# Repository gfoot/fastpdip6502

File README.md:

# Fast PDIP 6502 project sources

This is my attempt at making a fast 6502-based computer, overclocking the CPU to 32MHz and 
beyond, while retaining a 70s/80s-style parallel architecture, with ISA-style expansion slots,
using only PDIP and through-hole components.

See https://hackaday.io/project/192630-fast-pdip-6502-computer for more details including
photos, schematics, and a more complete description of the development and theory of the
project.

This repository contains:

* hardware/breadboard - schematics and "PCB" layout files for the breadboard prototype
* hardware/pcb - schematics, PCB layouts, gerbers, etc for the all the PCBs
* pld - various PLD module code required by different versions
* server - Python serial server code
* src - 6502 assembler code
* utils - other utility scripts

See also other READMEs:
* [src/README.md](src/README.md)
* [hardware/pcb/README.md](hardware/pcb/README.md)
* [hardware/breadboard/README.md](hardware/breadboard/README.md)

# Building

The hardware files need to be loaded into KiCad 7.0 for editing, exporting gerbers, etc.

The gerber zips can be sent straight to a PCB manufacturer if you just want the same PCBs that
I am using.

The PLD files are built using WinCupl.  I do this from the command line but you can also do it
in the GUI if you prefer.

The 6502 assembler source is built using xa, which is easy to install under Ubuntu at least.  One build
step requires use of Python to create a #include file - I use Python 3 for this.  There's a Makefile in
the "src" directory.

The serial server program is also written in Python, for Python 3.

All of this is run on Ubuntu Linux but you should be able to port it to other systems.

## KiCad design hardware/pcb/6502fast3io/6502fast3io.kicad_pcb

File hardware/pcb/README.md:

# PCB design files

There are various KiCad projects that together make up the system.  The I/O module and CPU module are required
of course, the others are optional add-ons.

The gerbers for all the revisions I've made ("issues") are also included, along with exported schematics in PDF and PNG files
correspsonding to those revisions for easy reference.

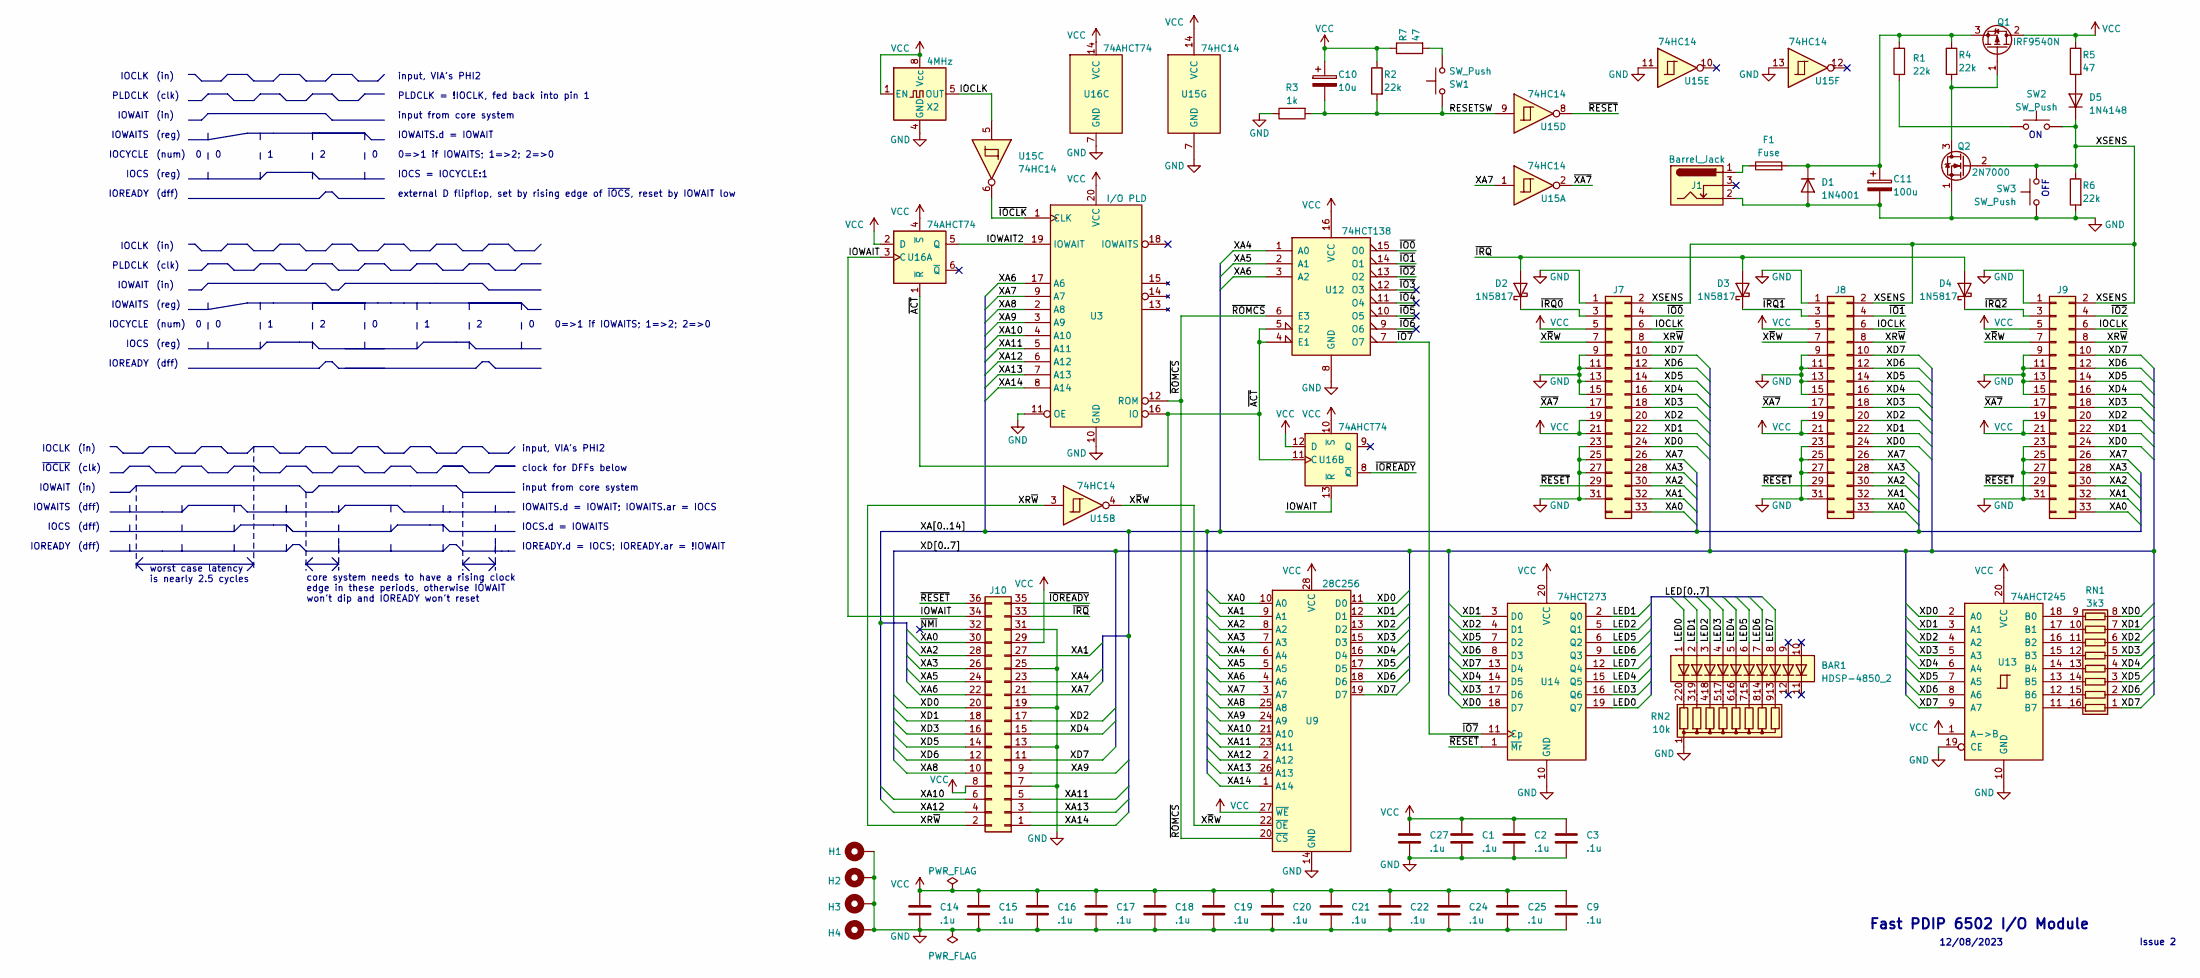
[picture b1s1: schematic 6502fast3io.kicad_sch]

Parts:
BAR1: HDSP-4850_2; HDSP-4850
C1, C2, C3, C9, C14, C15, C16, C17, C18, C19, C20, C21, C22, C24, C25, C27: .1u; C_Disc_D3.0mm_W1.6mm_P2.50mm
C10: 10u; CP_Radial_D5.0mm_P2.00mm
C11: 100u; CP_Radial_D5.0mm_P2.00mm
D1: 1N4001; D_DO-41_SOD81_P10.16mm_Horizontal
D2, D3, D4: 1N5817; D_DO-34_SOD68_P7.62mm_Horizontal
D5: 1N4148; D_DO-34_SOD68_P10.16mm_Horizontal
F1: Fuse; R_Axial_DIN0207_L6.3mm_D2.5mm_P10.16mm_Horizontal
H1, H2, H3, H4: MountingHole_Pad; MountingHole_2.2mm_M2_Pad
J1: Barrel_Jack; BarrelJack_Horizontal
J7, J8, J9: conn_pcb_edge_33pin_sense; 6502fast2_IO_PCBEdgeSocket
J10: Conn_02x18_Odd_Even; PCB_Edge_Socket_36pin
Q1: IRF9540N; TO-220-3_Horizontal_TabDown_NoHole
Q2: 2N7000; TO-92_Inline
R1, R2, R4, R6: 22k; R_Axial_DIN0204_L3.6mm_D1.6mm_P7.62mm_Horizontal
R3: 1k; R_Axial_DIN0204_L3.6mm_D1.6mm_P7.62mm_Horizontal
R5, R7: 47; R_Axial_DIN0204_L3.6mm_D1.6mm_P7.62mm_Horizontal
RN1: 3k3; DIP-16_W7.62mm
RN2: 10k; R_Array_SIP9
SW1, SW2, SW3: SW_Push; SW_PUSH_6mm_H4.3mm
U3: I/O PLD; DIP-20_W7.62mm_Socket
U9: 28C256; DIP-28_W15.24mm_Socket
U12: 74HCT138; DIP-16_W7.62mm
U13: 74AHCT245; DIP-20_W7.62mm
U14: 74HCT273; DIP-20_W7.62mm
U15: 74HC14; DIP-14_W7.62mm
U16: 74AHCT74; DIP-14_W7.62mm
X2: 4MHz; Oscillator_DIP-8

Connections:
/IOCLK: J7.6, J8.6, J9.6, U15.5, X2.5 (OUT)
/IOWAIT: J10.34, U16.3 (C), U16.13 (~R)
/IOWAIT2: U3.19 (IOWAIT), U16.5 (Q)
/LED0: BAR1.1 (A), U14.19 (Q7)
/LED1: BAR1.2 (A), U14.2 (Q0)
/LED2: BAR1.3 (A), U14.5 (Q1)
/LED3: BAR1.4 (A), U14.16 (Q6)
/LED4: BAR1.5 (A), U14.15 (Q5)
/LED5: BAR1.6 (A), U14.6 (Q2)
/LED6: BAR1.7 (A), U14.9 (Q3)
/LED7: BAR1.8 (A), U14.12 (Q4)
/RESETSW: C10.2, R2.2, R3.2, SW1.2, U15.9
/XA0: J7.33, J8.33, J9.33, J10.30, U9.10 (A0)
/XA1: J7.32, J8.32, J9.32, J10.27, U9.9 (A1)
/XA2: J7.30, J8.30, J9.30, J10.28, U9.8 (A2)
/XA3: J7.28, J8.28, J9.28, J10.26, U9.7 (A3)
/XA4: J10.23, U9.6 (A4), U12.1 (A0)
/XA5: J10.24, U9.5 (A5), U12.2 (A1)
/XA6: J10.22, U3.17 (A6), U9.4 (A6), U12.3 (A2)
/XA7: J7.26, J8.26, J9.26, J10.21, U3.9 (A7), U9.3 (A7), U15.1
/XA8: J10.10, U3.2 (A8), U9.25 (A8)
/XA9: J10.9, U3.3 (A9), U9.24 (A9)
/XA10: J10.6, U3.4 (A10), U9.21 (A10)
/XA11: J10.5, U3.5 (A11), U9.23 (A11)
/XA12: J10.4, U3.6 (A12), U9.2 (A12)
/XA13: J10.3, U3.7 (A13), U9.26 (A13)
/XA14: J10.1, U3.8 (A14), U9.1 (A14)
/XD0: J7.24, J8.24, J9.24, J10.20, RN1.8 (R8.1), U9.11 (D0), U13.2 (A0), U14.18 (D7)
/XD1: J7.22, J8.22, J9.22, J10.18, RN1.7 (R7.1), U9.12 (D1), U13.3 (A1), U14.3 (D0)
/XD2: J7.20, J8.20, J9.20, J10.17, RN1.6 (R6.1), U9.13 (D2), U13.4 (A2), U14.4 (D1)
/XD3: J7.18, J8.18, J9.18, J10.16, RN1.5 (R5.1), U9.15 (D3), U13.5 (A3), U14.17 (D6)
/XD4: J7.16, J8.16, J9.16, J10.15, RN1.4 (R4.1), U9.16 (D4), U13.6 (A4), U14.14 (D5)
/XD5: J7.14, J8.14, J9.14, J10.14, RN1.3 (R3.1), U9.17 (D5), U13.7 (A5), U14.7 (D2)
/XD6: J7.12, J8.12, J9.12, J10.12, RN1.2 (R2.1), U9.18 (D6), U13.8 (A6), U14.8 (D3)
/XD7: J7.10, J8.10, J9.10, J10.11, RN1.1 (R1.1), U9.19 (D7), U13.9 (A7), U14.13 (D4)
/XR~W: J7.8, J8.8, J9.8, J10.2, U15.3
/XSENS: D5.1 (K), J7.2, J8.2, J9.2, Q2.2 (G), R6.1, SW2.2, SW3.2
/X~RW: J7.7, J8.7, J9.7, U9.22 (~OE), U15.4
/~ACT: U3.16 (IO), U12.4 (E1), U12.5 (E2), U16.1 (~R), U16.11 (C)
/~IO0: J7.4, U12.15 (O0)
/~IO1: J8.4, U12.14 (O1)
/~IO2: J9.4, U12.13 (O2)
/~IO3: U12.12 (O3)
/~IO4: U12.11 (O4)
/~IO5: U12.10 (O5)
/~IO6: U12.9 (O6)
/~IO7: U12.7 (O7), U14.11 (Cp)
/~IOCLK: U3.1 (CLK), U15.6
/~IOREADY: J10.35, U16.8 (~Q)
/~IRQ0: D2.1 (K), J7.3
/~IRQ1: D3.1 (K), J8.3
/~IRQ2: D4.1 (K), J9.3
/~IRQ: D2.2 (A), D3.2 (A), D4.2 (A), J10.33
/~NMI: J10.32
/~RESET: J7.29, J8.29, J9.29, J10.36, U14.1 (~Mr), U15.8
/~ROMCS: U3.12 (ROM), U9.20 (~CS), U12.6 (E3)
/~XA7: J7.17, J8.17, J9.17, U15.2
GND: C1.2, C2.2, C3.2, C9.2, C11.2, C14.2, C15.2, C16.2, C17.2, C18.2, C19.2, C20.2, C21.2, C22.2, C24.2, C25.2, C27.2, D1.2 (A), H1.1, H2.1, H3.1, H4.1, J1.2, J7.1, J7.9, J7.11, J7.13, J7.15, J7.23, J7.25, J7.27, J7.31, J8.1, J8.9, J8.11, J8.13, J8.15, J8.23, J8.25, J8.27, J8.31, J9.1, J9.9, J9.11, J9.13, J9.15, J9.23, J9.25, J9.27, J9.31, J10.7, J10.13, J10.19, J10.25, J10.31, Q2.1 (S), R3.1, R6.2, RN2.1 (common), SW3.1, U3.10 (GND), U3.11 (OE), U9.14 (GND), U12.8 (GND), U13.10 (GND), U13.19 (CE), U14.10 (GND), U15.7 (GND), U15.11, U15.13, U16.7 (GND), X2.4 (GND)
unnamed: C11.1, D1.1 (K), F1.2, Q1.3 (S), R1.1, R4.1
unnamed: D5.2 (A), R5.2
unnamed: F1.1, J1.1
unnamed: Q1.1 (G), Q2.3 (D), R4.2
unnamed: R1.2, SW2.1
unnamed: R7.2, SW1.1
unnamed: RN1.16 (R1.2), U13.11 (B7)
unnamed: RN1.15 (R2.2), U13.12 (B6)
unnamed: RN1.14 (R3.2), U13.13 (B5)
unnamed: RN1.13 (R4.2), U13.14 (B4)
unnamed: RN1.12 (R5.2), U13.15 (B3)
unnamed: RN1.11 (R6.2), U13.16 (B2)
unnamed: RN1.10 (R7.2), U13.17 (B1)
unnamed: RN1.9 (R8.2), U13.18 (B0)
unnamed: BAR1.20 (K), RN2.2 (R1)
unnamed: BAR1.19 (K), RN2.3 (R2)
unnamed: BAR1.18 (K), RN2.4 (R3)
unnamed: BAR1.17 (K), RN2.5 (R4)
unnamed: BAR1.16 (K), RN2.6 (R5)
unnamed: BAR1.15 (K), RN2.7 (R6)
unnamed: BAR1.14 (K), RN2.8 (R7)
unnamed: BAR1.13 (K), RN2.9 (R8)
VCC: C1.1, C2.1, C3.1, C9.1, C10.1, C14.1, C15.1, C16.1, C17.1, C18.1, C19.1, C20.1, C21.1, C22.1, C24.1, C25.1, C27.1, J7.5, J7.19, J7.21, J8.5, J8.19, J8.21, J9.5, J9.19, J9.21, J10.8, J10.29, Q1.2 (D), R2.1, R5.1, R7.1, U3.20 (VCC), U9.27 (~WE), U9.28 (VCC), U12.16 (VCC), U13.1 (A->B), U13.20 (VCC), U14.20 (VCC), U15.14 (VCC), U16.2 (D), U16.4 (~S), U16.10 (~S), U16.12 (D), U16.14 (VCC), X2.1 (EN), X2.8 (Vcc)

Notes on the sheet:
(num)
IOCLK
OFF
12/08/2023
(dff)
IOCYCLE
IOCS.d = IOWAITS
input from core system
IOREADY
(in)
IOWAITS
IOWAIT
IOWAITS.d = IOWAIT
IOCS
(clk)
external D flipflop, set by rising edge of ~{IOCS}, reset by IOWAIT low
PLDCLK = !IOCLK, fed back into pin 1
worst case latency is nearly 2.5 cycles
core system needs to have a rising clock edge in these periods, otherwise IOWAIT won't dip and IOREADY won't reset
clock for DFFs below
(reg)
IOREADY.d = IOCS; IOREADY.ar = !IOWAIT
Issue 2
0=>1 if IOWAITS; 1=>2; 2=>0
PLDCLK
IOCS = IOCYCLE:1
Fast PDIP 6502 I/O Module
input, VIA's PHI2
~{IOCLK}
IOWAITS.d = IOWAIT; IOWAITS.ar = IOCS

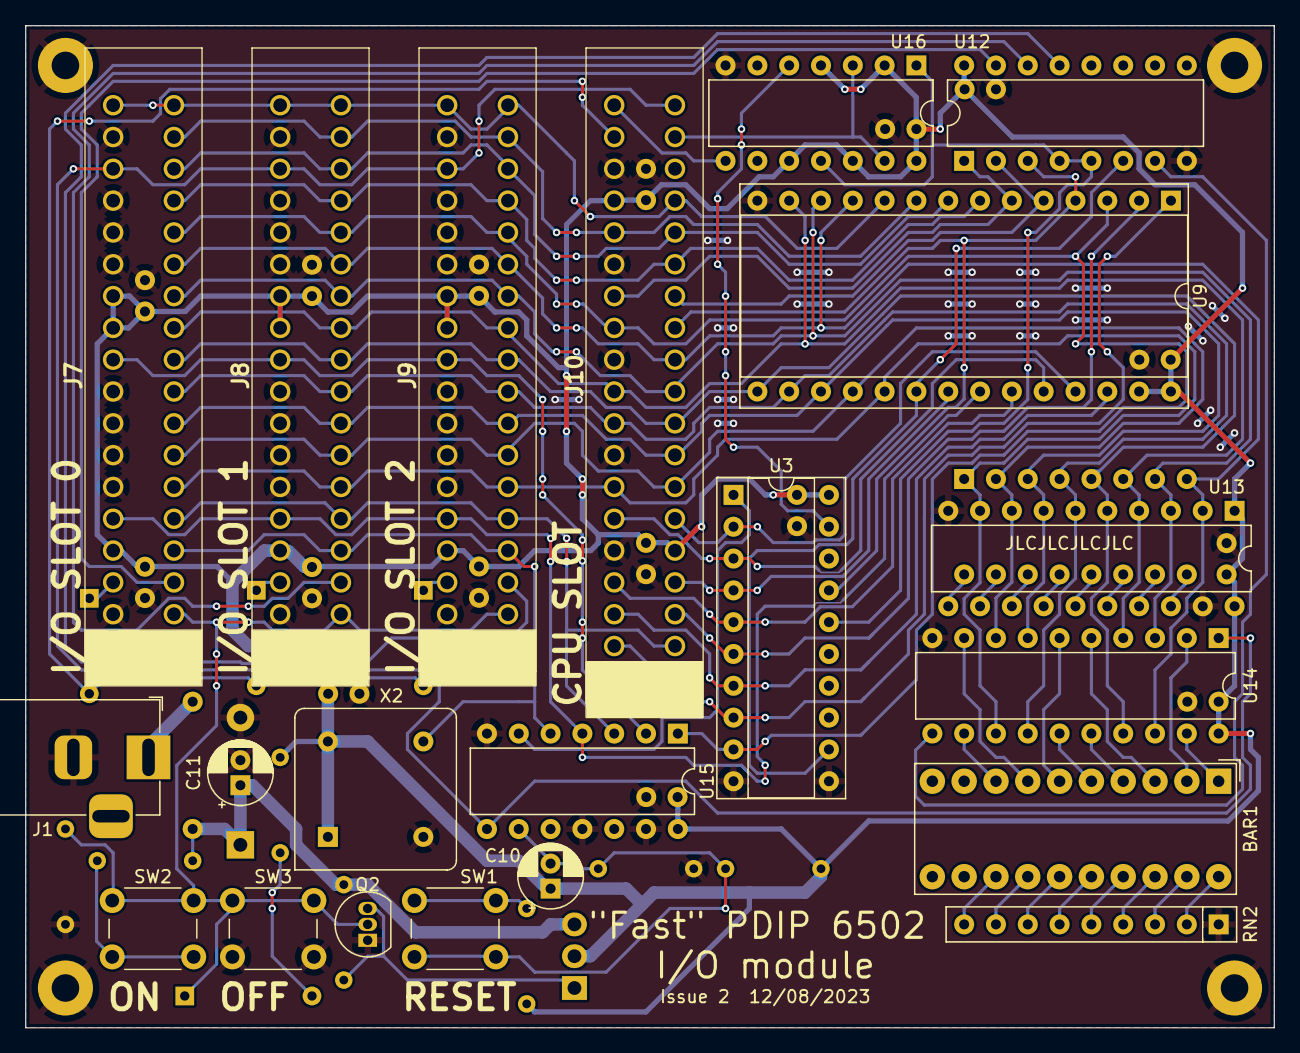
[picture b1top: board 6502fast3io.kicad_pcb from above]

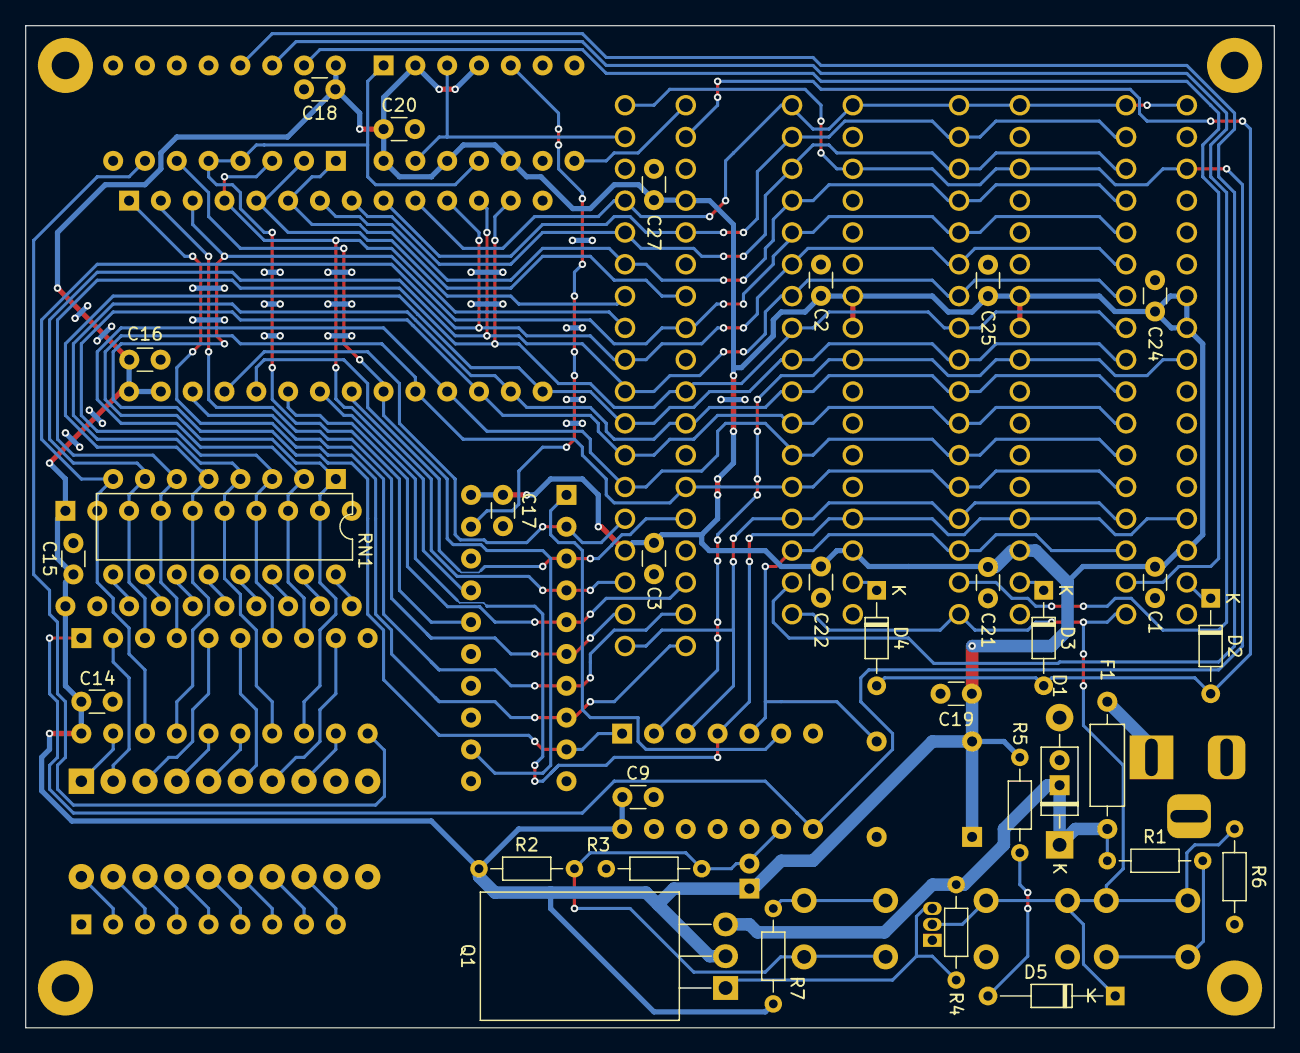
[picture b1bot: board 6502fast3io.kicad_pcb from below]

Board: 2 copper layers, 99.7 x 80.0 mm, 56 parts (31 on the bottom side), 76 nets.

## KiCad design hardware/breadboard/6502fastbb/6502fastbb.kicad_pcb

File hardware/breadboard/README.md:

# Breadboard circuit and layout

This project was used to define a slightly modified circuit for implementation on solderless
breadboards, and to plan the layout of the components.  It combines the CPU and I/O modules, but has
some parts removed which are only relevant to the PCB version such as I/O expansion sockets.

The PCB layout editor shows the positioning of the components on the breadboard, but not the connections between them.

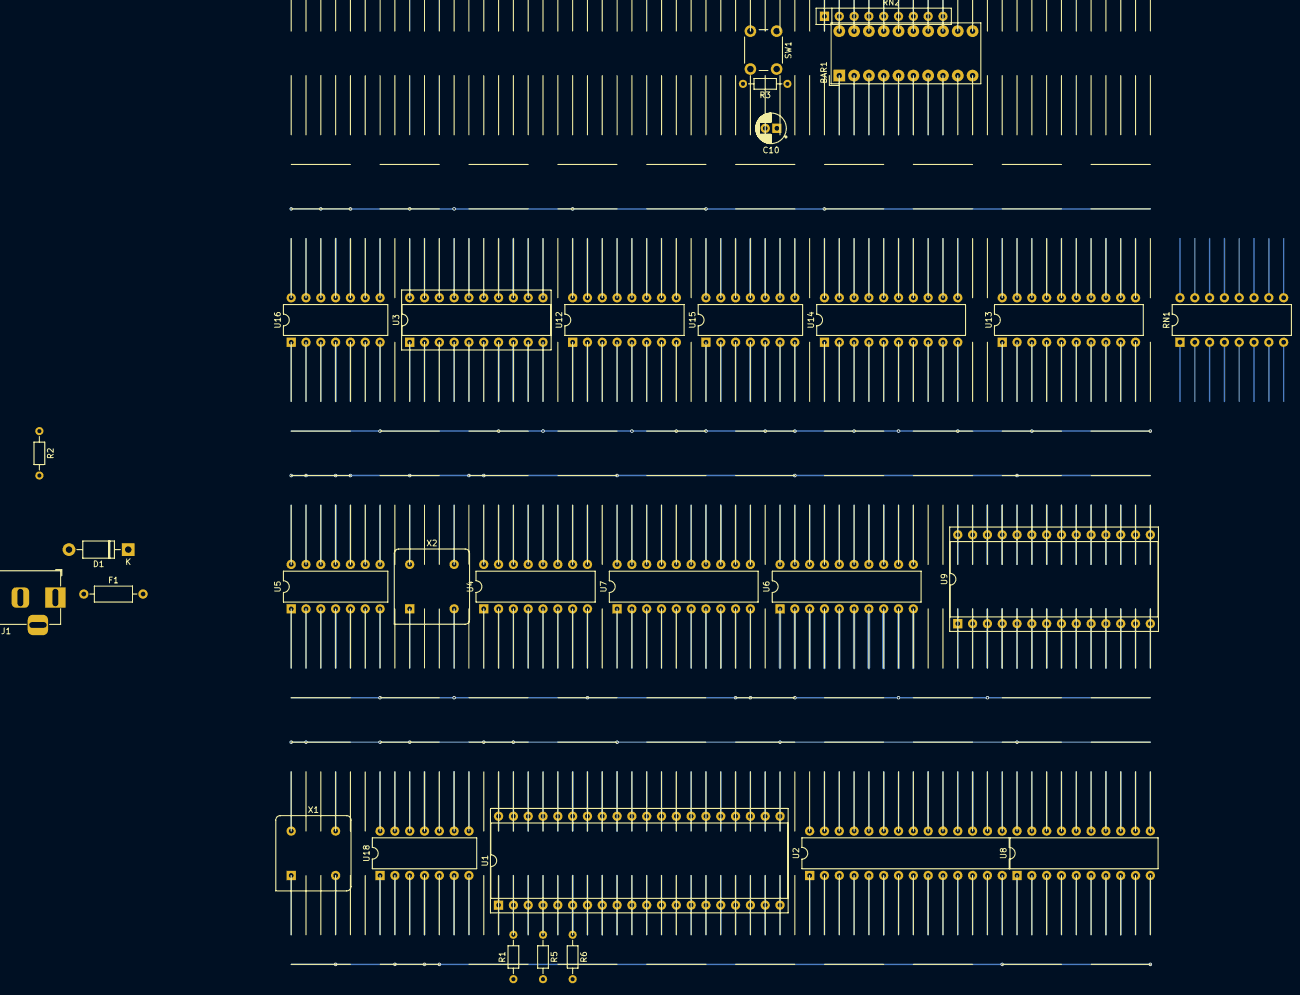
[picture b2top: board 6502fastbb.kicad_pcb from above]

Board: 2 copper layers, 30 parts (0 on the bottom side), 98 nets.

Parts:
BAR1: HDSP-4850_2; HDSP-4850
C10: 10u; CP_Radial_D5.0mm_P2.00mm
D1: 1N4001; D_DO-41_SOD81_P10.16mm_Horizontal
F1: Fuse; R_Axial_DIN0207_L6.3mm_D2.5mm_P10.16mm_Horizontal
J1: Barrel_Jack; BarrelJack_Horizontal
R1: 3k3; R_Axial_DIN0204_L3.6mm_D1.6mm_P7.62mm_Horizontal
R2: 1k; R_Axial_DIN0204_L3.6mm_D1.6mm_P7.62mm_Horizontal
R3: 22k; R_Axial_DIN0204_L3.6mm_D1.6mm_P7.62mm_Horizontal
R5, R6: 330; R_Axial_DIN0204_L3.6mm_D1.6mm_P7.62mm_Horizontal
RN1: 3k3; DIP-16_W7.62mm
RN2: 10k; R_Array_SIP9
SW1: SW_Push; SW_PUSH_6mm_H4.3mm
U1: WD65C02; DIP-40_W15.24mm_Socket
U2: 71256; DIP-28_W7.62mm
U3: I/O PLD; DIP-20_W7.62mm_Socket
U4: 74AHCT139; DIP-16_W7.62mm
U5: 74HC74; DIP-14_W7.62mm
U6, U7, U8: 74HC245; DIP-20_W7.62mm
U9: 28C256; DIP-28_W15.24mm_Socket
U12: 74HCT138; DIP-16_W7.62mm
U13: 74AHCT245; DIP-20_W7.62mm
U14: 74HCT273; DIP-20_W7.62mm
U15: 74HC14; DIP-14_W7.62mm
U16: 74AHCT74; DIP-14_W7.62mm
U18: 74LS32; DIP-14_W7.62mm
X1: CXO_DIP8; Oscillator_DIP-8
X2: 4MHz; Oscillator_DIP-8

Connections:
/A0: U1.9 (A0), U2.1 (A14), U7.2 (A0)
/A1: U1.10 (A1), U2.2 (A12), U7.3 (A1)
/A2: U1.11 (A2), U2.3 (A7), U7.4 (A2)
/A3: U1.12 (A3), U2.4 (A6), U7.5 (A3)
/A4: U1.13 (A4), U2.5 (A5), U7.6 (A4)
/A5: U1.14 (A5), U2.6 (A4), U7.7 (A5)
/A6: U1.15 (A6), U2.7 (A3), U7.8 (A6)
/A7: U1.16 (A7), U2.21 (A10), U6.2 (A0)
/A8: U1.17 (A8), U2.8 (A2), U6.3 (A1)
/A9: U1.18 (A9), U2.9 (A1), U6.4 (A2)
/A10: U1.19 (A10), U2.10 (A0), U6.5 (A3)
/A11: U1.20 (A11), U2.23 (A11), U6.6 (A4)
/A12: U1.22 (A12), U2.24 (A9), U6.7 (A5)
/A13: U1.23 (A13), U2.25 (A8), U6.8 (A6)
/A14: U1.24 (A14), U2.26 (A13), U6.9 (A7)
/A15: U1.25 (A15), U4.1 (E), U4.14 (A0), U5.12 (D)
/CLK: U18.9, U18.12, X1.5 (OUT)
/D0: U1.33 (D0), U2.15 (Q3), U8.2 (A0)
/D1: U1.32 (D1), U2.13 (Q2), U8.3 (A1)
/D2: U1.31 (D2), U2.16 (Q4), U8.4 (A2)
/D3: U1.30 (D3), U2.17 (Q5), U8.5 (A3)
/D4: U1.29 (D4), U2.18 (Q6), U8.6 (A4)
/D5: U1.28 (D5), U2.19 (Q7), U8.7 (A5)
/D6: U1.27 (D6), U2.12 (Q1), U8.8 (A6)
/D7: U1.26 (D7), U2.11 (Q0), U8.9 (A7)
/DCLK: U5.3 (C), U5.11 (C), U18.3
/IO module/IOWAIT2: U3.19 (IOWAIT), U16.5 (Q)
/IO module/LED0: BAR1.1 (A), U14.19 (Q7)
/IO module/LED1: BAR1.2 (A), U14.2 (Q0)
/IO module/LED2: BAR1.3 (A), U14.5 (Q1)
/IO module/LED3: BAR1.4 (A), U14.16 (Q6)
/IO module/LED4: BAR1.5 (A), U14.15 (Q5)
/IO module/LED5: BAR1.6 (A), U14.6 (Q2)
/IO module/LED6: BAR1.7 (A), U14.9 (Q3)
/IO module/LED7: BAR1.8 (A), U14.12 (Q4)
/IO module/RESETSW: C10.2, R2.2, R3.2, SW1.2, U15.9
/IO module/X~RW: U9.22 (~OE), U15.4
/IO module/~ACT: U3.16 (IO), U12.4 (E1), U12.5 (E2), U16.1 (~R), U16.11 (C)
/IO module/~IO7: U12.7 (O7), U14.11 (Cp)
/IO module/~IOCLK: U3.1 (CLK), X2.5 (OUT)
/IO module/~ROMCS: U3.12 (ROM), U9.20 (~CS), U12.6 (E3)
/IOWAIT: U5.4 (~S), U5.9 (Q), U16.3 (C), U16.13 (~R)
/PHI2: U1.37 (PHI2), U4.3 (A1), U18.8
/R~W: U1.34 (R/~W), U4.2 (A0), U4.13 (A1), U7.9 (A7)
/XA0: U7.18 (B0), U9.10 (A0)
/XA1: U7.17 (B1), U9.9 (A1)
/XA2: U7.16 (B2), U9.8 (A2)
/XA3: U7.15 (B3), U9.7 (A3)
/XA4: U7.14 (B4), U9.6 (A4), U12.1 (A0)
/XA5: U7.13 (B5), U9.5 (A5), U12.2 (A1)
/XA6: U3.17 (A6), U7.12 (B6), U9.4 (A6), U12.3 (A2)
/XA7: U3.9 (A7), U6.18 (B0), U9.3 (A7)
/XA8: U3.2 (A8), U6.17 (B1), U9.25 (A8)
/XA9: U3.3 (A9), U6.16 (B2), U9.24 (A9)
/XA10: U3.4 (A10), U6.15 (B3), U9.21 (A10)
/XA11: U3.5 (A11), U6.14 (B4), U9.23 (A11)
/XA12: U3.6 (A12), U6.13 (B5), U9.2 (A12)
/XA13: U3.7 (A13), U6.12 (B6), U9.26 (A13)
/XA14: U3.8 (A14), U6.11 (B7), U9.1 (A14)
/XD0: RN1.8 (R8.1), U8.18 (B0), U9.11 (D0), U13.2 (A0), U14.18 (D7)
/XD1: RN1.7 (R7.1), U8.17 (B1), U9.12 (D1), U13.3 (A1), U14.3 (D0)
/XD2: RN1.6 (R6.1), U8.16 (B2), U9.13 (D2), U13.4 (A2), U14.4 (D1)
/XD3: RN1.5 (R5.1), U8.15 (B3), U9.15 (D3), U13.5 (A3), U14.17 (D6)
/XD4: RN1.4 (R4.1), U8.14 (B4), U9.16 (D4), U13.6 (A4), U14.14 (D5)
/XD5: RN1.3 (R3.1), U8.13 (B5), U9.17 (D5), U13.7 (A5), U14.7 (D2)
/XD6: RN1.2 (R2.1), U8.12 (B6), U9.18 (D6), U13.8 (A6), U14.8 (D3)
/XD7: RN1.1 (R1.1), U8.11 (B7), U9.19 (D7), U13.9 (A7), U14.13 (D4)
/XR~W: U7.11 (B7), U15.3
/~IORD: U4.9 (O3), U8.1 (A->B)
/~IOREADY: U5.2 (D), U16.8 (~Q)
/~IOWAIT: U5.8 (~Q), U18.10
/~IRQ: R5.1, U1.4 (~IRQ)
/~NMI: R6.1, U1.6 (~NMI)
/~RAMOE: U2.22 (~OE), U4.7 (O3)
/~RAMWE: U2.27 (~WE), U4.6 (O2)
/~RDYRESET: U5.5 (Q), U5.13 (~R)
/~RESET: U1.40 (~RESET), U14.1 (~Mr), U15.8
GND: D1.2 (A), J1.2, R2.1, RN2.1 (common), U1.21 (GND), U2.14 (GND), U2.20 (~CS), U3.10 (GND), U3.11 (OE), U4.8 (GND), U4.15 (E), U5.7 (GND), U6.10 (GND), U6.19 (CE), U7.10 (GND), U7.19 (CE), U8.10 (GND), U8.19 (CE), U9.14 (GND), U12.8 (GND), U13.10 (GND), U13.19 (CE), U14.10 (GND), U15.1, U15.5, U15.7 (GND), U15.11, U15.13, U16.7 (GND), U18.2, U18.4, U18.5, U18.7 (GND), U18.13, X1.4 (GND), X2.4 (GND)
unnamed: F1.1, J1.1
unnamed: RN1.16 (R1.2), U13.11 (B7)
unnamed: RN1.15 (R2.2), U13.12 (B6)
unnamed: RN1.14 (R3.2), U13.13 (B5)
unnamed: RN1.13 (R4.2), U13.14 (B4)
unnamed: RN1.12 (R5.2), U13.15 (B3)
unnamed: RN1.11 (R6.2), U13.16 (B2)
unnamed: RN1.10 (R7.2), U13.17 (B1)
unnamed: RN1.9 (R8.2), U13.18 (B0)
unnamed: BAR1.20 (K), RN2.2 (R1)
unnamed: BAR1.19 (K), RN2.3 (R2)
unnamed: BAR1.18 (K), RN2.4 (R3)
unnamed: BAR1.17 (K), RN2.5 (R4)
unnamed: BAR1.16 (K), RN2.6 (R5)
unnamed: BAR1.15 (K), RN2.7 (R6)
unnamed: BAR1.14 (K), RN2.8 (R7)
unnamed: BAR1.13 (K), RN2.9 (R8)
unnamed: R1.2, U1.2 (RDY)
unnamed: U18.1, U18.11
VCC: C10.1, D1.1 (K), F1.2, R1.1, R3.1, R5.2, R6.2, SW1.1, U1.8 (VCC), U1.36 (BE), U1.38 (~SO), U2.28 (VCC), U3.20 (VCC), U4.16 (VCC), U5.1 (~R), U5.10 (~S), U5.14 (VCC), U6.1 (A->B), U6.20 (VCC), U7.1 (A->B), U7.20 (VCC), U8.20 (VCC), U9.27 (~WE), U9.28 (VCC), U12.16 (VCC), U13.1 (A->B), U13.20 (VCC), U14.20 (VCC), U15.14 (VCC), U16.2 (D), U16.4 (~S), U16.10 (~S), U16.12 (D), U16.14 (VCC), U18.14 (VCC), X1.1 (EN), X1.8 (Vcc), X2.1 (EN), X2.8 (Vcc)

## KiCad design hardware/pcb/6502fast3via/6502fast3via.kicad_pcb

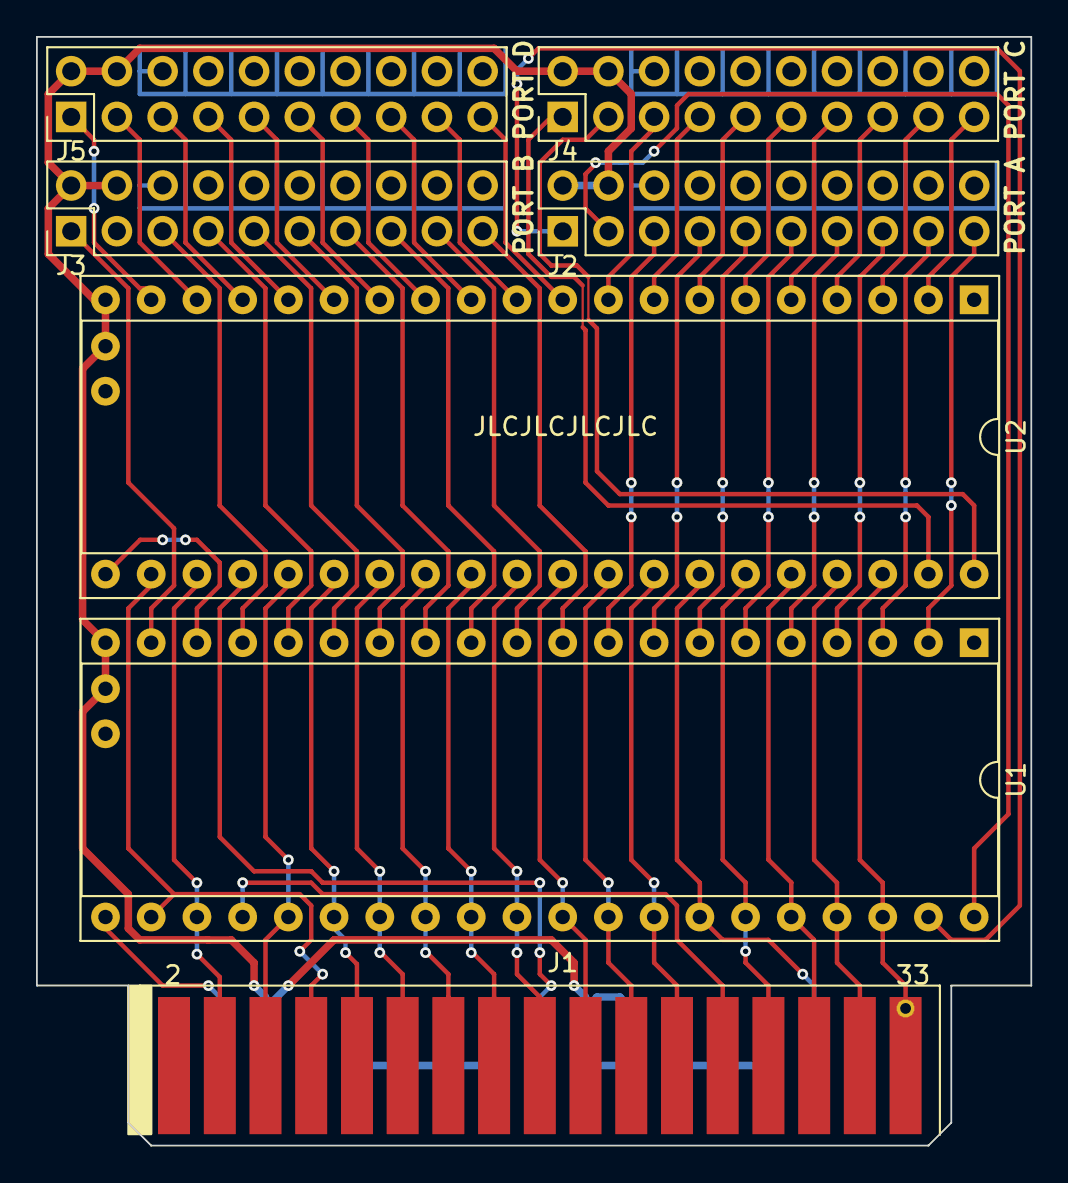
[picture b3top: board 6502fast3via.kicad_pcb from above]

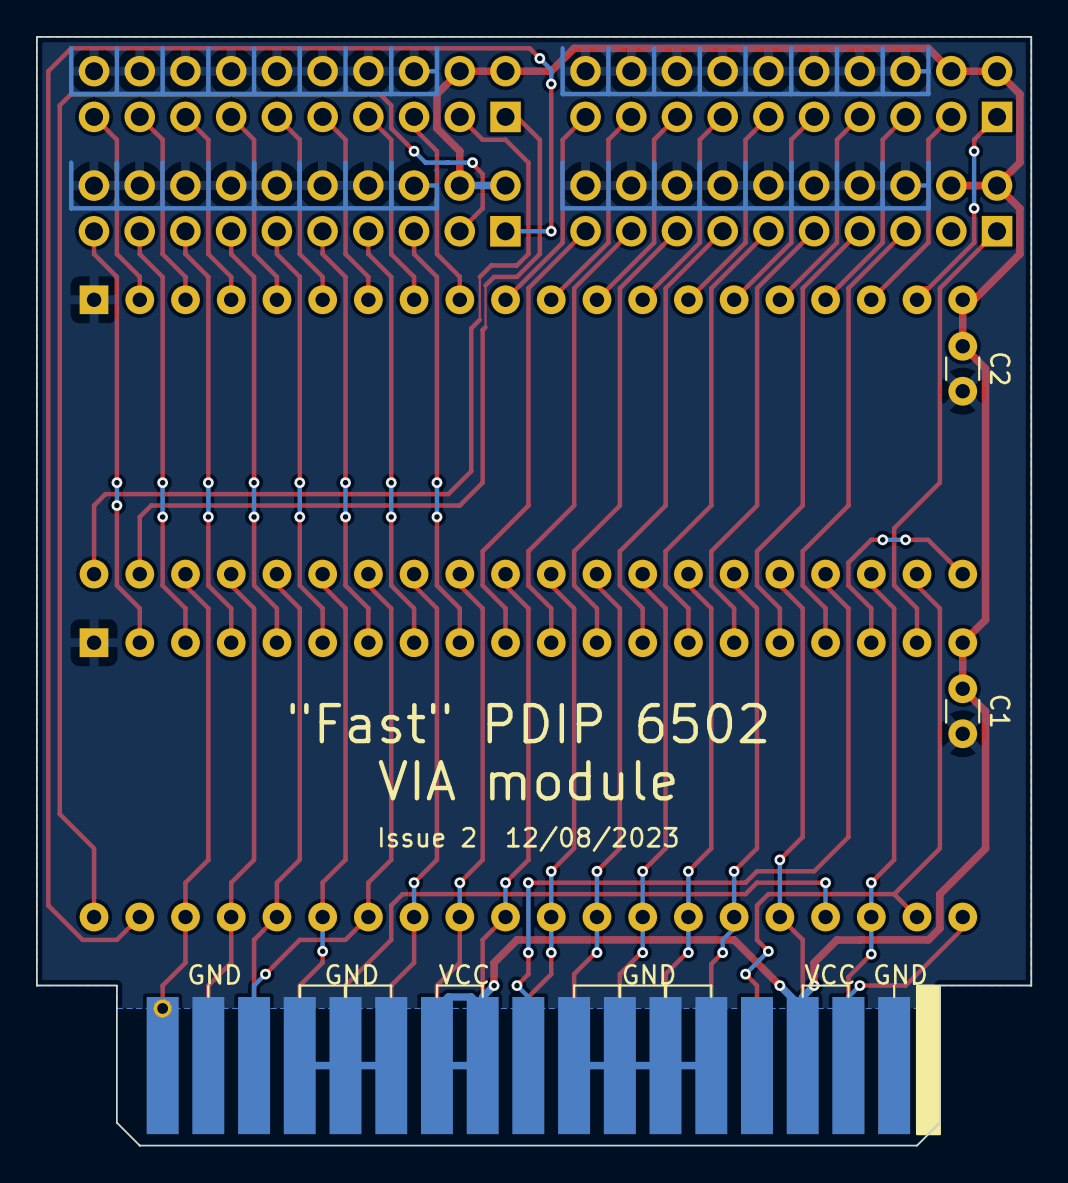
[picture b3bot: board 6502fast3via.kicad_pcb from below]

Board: 2 copper layers, 55.2 x 61.6 mm, 9 parts (2 on the bottom side), 61 nets.

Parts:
C1, C2: .1u; C_Disc_D3.0mm_W1.6mm_P2.50mm
J1: conn_pcb_edge_33pin_sense; 6502fast2_IO_PCBEdge
J2, J3, J4, J5: Conn_02x10_Odd_Even; PinHeader_2x10_P2.54mm_Vertical
U1, U2: WD65C22; DIP-40_W15.24mm_Socket

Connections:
/CA1: J2.3, U1.40 (CA1)
/CA2: J2.1, U1.39 (CA2)
/CB1: U1.18 (CB1), U2.21 (~IRQ)
/CB2: J3.1, U1.19 (CB2)
/CC1: J4.3, U2.40 (CA1)
/CC2: J4.1, U2.39 (CA2)
/CD1: J5.3, U2.18 (CB1)
/CD2: J5.1, U2.19 (CB2)
/PA0: J2.19, U1.2 (PA0)
/PA1: J2.17, U1.3 (PA1)
/PA2: J2.15, U1.4 (PA2)
/PA3: J2.13, U1.5 (PA3)
/PA4: J2.11, U1.6 (PA4)
/PA5: J2.9, U1.7 (PA5)
/PA6: J2.7, U1.8 (PA6)
/PA7: J2.5, U1.9 (PA7)
/PB0: J3.19, U1.10 (PB0)
/PB1: J3.17, U1.11 (PB1)
/PB2: J3.15, U1.12 (PB2)
/PB3: J3.13, U1.13 (PB3)
/PB4: J3.11, U1.14 (PB4)
/PB5: J3.9, U1.15 (PB5)
/PB6: J3.7, U1.16 (PB6)
/PB7: J3.5, U1.17 (PB7)
/PC0: J4.19, U2.2 (PA0)
/PC1: J4.17, U2.3 (PA1)
/PC2: J4.15, U2.4 (PA2)
/PC3: J4.13, U2.5 (PA3)
/PC4: J4.11, U2.6 (PA4)
/PC5: J4.9, U2.7 (PA5)
/PC6: J4.7, U2.8 (PA6)
/PC7: J4.5, U2.9 (PA7)
/PD0: J5.19, U2.10 (PB0)
/PD1: J5.17, U2.11 (PB1)
/PD2: J5.15, U2.12 (PB2)
/PD3: J5.13, U2.13 (PB3)
/PD4: J5.11, U2.14 (PB4)
/PD5: J5.9, U2.15 (PB5)
/PD6: J5.7, U2.16 (PB6)
/PD7: J5.5, U2.17 (PB7)
/VA0: J1.33, U1.38 (RS0), U2.38 (RS0)
/VA1: J1.32, U1.37 (RS1), U2.37 (RS1)
/VA2: J1.30, U1.36 (RS2), U2.36 (RS2)
/VA3: J1.28, U1.35 (RS3), U2.35 (RS3)
/VA7: J1.26, U1.24 (CS1)
/VCLK: J1.6, U1.25 (PHI2), U2.25 (PHI2)
/VD0: J1.24, U1.33 (D0), U2.33 (D0)
/VD1: J1.22, U1.32 (D1), U2.32 (D1)
/VD2: J1.20, U1.31 (D2), U2.31 (D2)
/VD3: J1.18, U1.30 (D3), U2.30 (D3)
/VD4: J1.16, U1.29 (D4), U2.29 (D4)
/VD5: J1.14, U1.28 (D5), U2.28 (D5)
/VD6: J1.12, U1.27 (D6), U2.27 (D6)
/VD7: J1.10, U1.26 (D7), U2.26 (D7)
/VR~W: J1.8, U1.22 (R/~W), U2.22 (R/~W)
/~VA7: J1.17, U2.24 (CS1)
/~VCS: J1.4, U1.23 (~CS2), U2.23 (~CS2)
/~VIRQ: J1.3, U1.21 (~IRQ)
/~VRESET: J1.29, U1.34 (~RESET), U2.34 (~RESET)
GND1: C1.2, C2.2, J1.1, J1.9, J1.11, J1.13, J1.15, J1.23, J1.25, J1.27, J1.31, J2.6, J2.8, J2.10, J2.12, J2.14, J2.16, J2.18, J2.20, J3.6, J3.8, J3.10, J3.12, J3.14, J3.16, J3.18, J3.20, J4.6, J4.8, J4.10, J4.12, J4.14, J4.16, J4.18, J4.20, J5.6, J5.8, J5.10, J5.12, J5.14, J5.16, J5.18, J5.20, U1.1 (GND), U2.1 (GND)
VCCQ: C1.1, C2.1, J1.5, J1.19, J1.21, J2.2, J2.4, J3.2, J3.4, J4.2, J4.4, J5.2, J5.4, U1.20 (VCC), U2.20 (VCC)

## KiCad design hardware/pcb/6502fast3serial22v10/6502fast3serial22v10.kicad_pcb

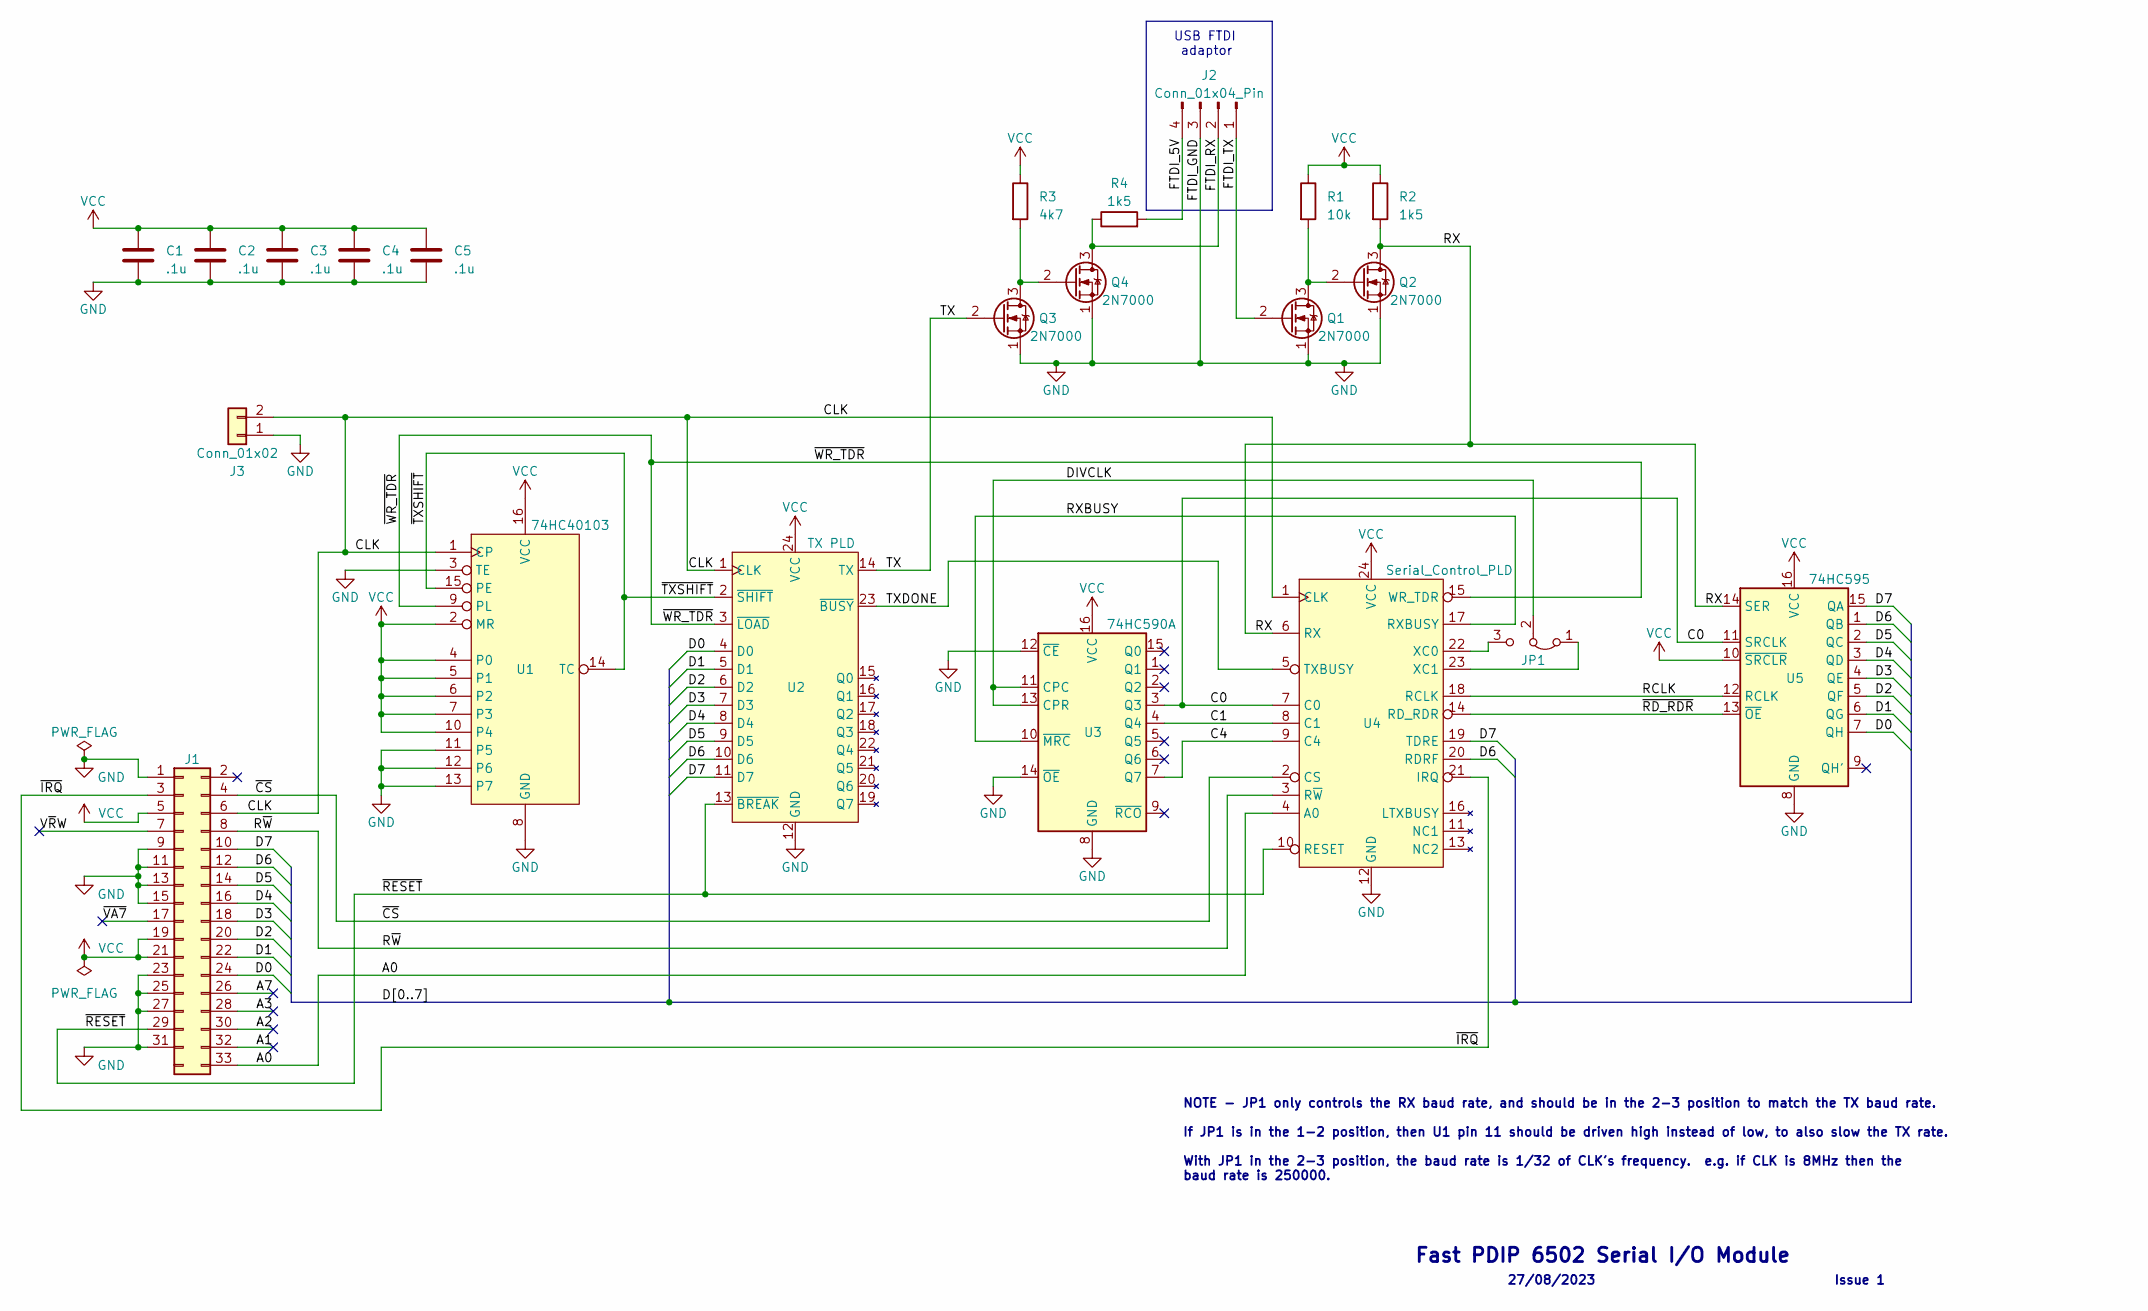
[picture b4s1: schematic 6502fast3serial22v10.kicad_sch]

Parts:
C1, C2, C3, C4, C5: .1u; C_Disc_D3.8mm_W2.6mm_P2.50mm
J1: conn_pcb_edge_33pin_sense; PCB_Edge_33pin_sense
J2: Conn_01x04_Pin; PinHeader_1x04_P2.54mm_Horizontal
J3: Conn_01x02; PinHeader_1x02_P2.54mm_Vertical
JP1: Jumper_3_Bridged12; PinHeader_1x03_P2.54mm_Horizontal
Q1, Q2, Q3, Q4: 2N7000; TO-92_Inline
R1: 10k; R_Axial_DIN0204_L3.6mm_D1.6mm_P7.62mm_Horizontal
R2, R4: 1k5; R_Axial_DIN0204_L3.6mm_D1.6mm_P7.62mm_Horizontal
R3: 4k7; R_Axial_DIN0204_L3.6mm_D1.6mm_P7.62mm_Horizontal
U1: 74HC40103; DIP-16_W7.62mm
U2: TX PLD; DIP-24_W7.62mm
U3: 74HC590A; DIP-16_W7.62mm
U4: Serial_Control_PLD; DIP-24_W7.62mm
U5: 74HC595; DIP-16_W7.62mm

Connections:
/A0: J1.33, U4.4 (A0)
/A1: J1.32
/A2: J1.30
/A3: J1.28
/A7: J1.26
/C0: U3.3 (Q3), U4.7 (C0), U5.11 (SRCLK)
/C1: U3.4 (Q4), U4.8 (C1)
/C4: U3.7 (Q7), U4.9 (C4)
/CLK: J1.6, J3.2, U1.1 (CP), U2.1 (CLK), U4.1 (CLK)
/D0: J1.24, U2.4 (D0), U5.7 (QH)
/D1: J1.22, U2.5 (D1), U5.6 (QG)
/D2: J1.20, U2.6 (D2), U5.5 (QF)
/D3: J1.18, U2.7 (D3), U5.4 (QE)
/D4: J1.16, U2.8 (D4), U5.3 (QD)
/D5: J1.14, U2.9 (D5), U5.2 (QC)
/D6: J1.12, U2.10 (D6), U4.20 (RDRF), U5.1 (QB)
/D7: J1.10, U2.11 (D7), U4.19 (TDRE), U5.15 (QA)
/DIVCLK: JP1.2 (C), U3.11 (CPC), U3.13 (CPR)
/FTDI_5V: J2.4, R4.2
/FTDI_RX: J2.2, Q4.3 (D), R4.1
/FTDI_TX: J2.1, Q1.2 (G)
/RCLK: U4.18 (RCLK), U5.12 (RCLK)
/RX: Q2.3 (D), R2.2, U4.6 (RX), U5.14 (SER)
/RXBUSY: U3.10 (~MRC), U4.17 (RXBUSY)
/R~W: J1.8, U4.3 (R~W)
/TX: Q3.2 (G), U2.14 (TX)
/TXDONE: U2.23 (~BUSY), U4.5 (TXBUSY)
/V~RW: J1.7
/~CS: J1.4, U4.2 (CS)
/~IRQ: J1.3, U4.21 (IRQ)
/~RD_RDR: U4.14 (RD_RDR), U5.13 (~OE)
/~RESET: J1.29, U2.13 (~BREAK), U4.10 (RESET)
/~TXSHIFT: U1.14 (TC), U1.15 (PE), U2.2 (~SHIFT)
/~VA7: J1.17
/~WR_TDR: U1.9 (PL), U2.3 (~LOAD), U4.15 (WR_TDR)
GND: C1.2, C2.2, C3.2, C4.2, C5.2, J1.1, J1.9, J1.11, J1.13, J1.15, J1.23, J1.25, J1.27, J1.31, J2.3, J3.1, Q1.1 (S), Q2.1 (S), Q3.1 (S), Q4.1 (S), U1.3 (TE), U1.8 (GND), U1.11 (P5), U1.12 (P6), U1.13 (P7), U2.12 (GND), U3.8 (GND), U3.12 (~CE), U3.14 (~OE), U4.12 (GND), U5.8 (GND)
unnamed: JP1.1 (A), U4.23 (XC1)
unnamed: JP1.3 (B), U4.22 (XC0)
unnamed: Q1.3 (D), Q2.2 (G), R1.2
unnamed: Q3.3 (D), Q4.2 (G), R3.2
VCC: C1.1, C2.1, C3.1, C4.1, C5.1, J1.5, J1.19, J1.21, R1.1, R2.1, R3.1, U1.2 (MR), U1.4 (P0), U1.5 (P1), U1.6 (P2), U1.7 (P3), U1.10 (P4), U1.16 (VCC), U2.24 (VCC), U3.16 (VCC), U4.24 (VCC), U5.10 (~SRCLR), U5.16 (VCC)

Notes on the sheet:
NOTE - JP1 only controls the RX baud rate, and should be in the 2-3 position to match the TX baud rate. If JP1 is in the 1-2 position, then U1 pin 11 should be driven high instead of low, to also slow the TX rate. With JP1 in the 2-3 position, the baud rate is 1/32 of CLK's frequency. e.g. if CLK i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
USB FTDI adaptor
27/08/2023
Fast PDIP 6502 Serial I/O Module
Issue 1
